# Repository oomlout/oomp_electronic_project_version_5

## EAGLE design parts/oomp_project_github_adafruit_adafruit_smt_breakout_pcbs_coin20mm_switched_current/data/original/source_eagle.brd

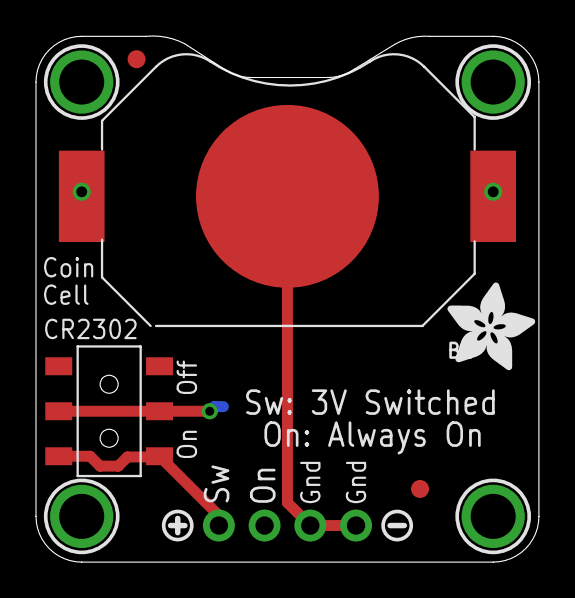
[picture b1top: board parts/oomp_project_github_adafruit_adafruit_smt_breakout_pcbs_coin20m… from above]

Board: 2 copper layers, 27.9 x 29.2 mm, 12 parts (0 on the bottom side), 3 nets.

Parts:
B1: CR2032_SMT_BAT-HLD-001
CN1: 1X4-CLEANBIG; 1X04-CLEANBIG
FID1, FID2: FIDUCIAL""; FIDUCIAL_1MM
SW1: EG1390
U$1, U$2, U$3, U$5: MOUNTINGHOLE2.5; MOUNTINGHOLE_2.5_PLATED
U$6: SYMBOL_PLUS
U$7: SYMBOL_MINUS
U$8: ADAFRUIT_5MM

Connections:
3V: B1.+$1, B1.+$2, CN1.3, SW1.P1, SW1.P2
GND: B1.-, CN1.1, CN1.2
unnamed: CN1.4, SW1.S1, SW1.S2

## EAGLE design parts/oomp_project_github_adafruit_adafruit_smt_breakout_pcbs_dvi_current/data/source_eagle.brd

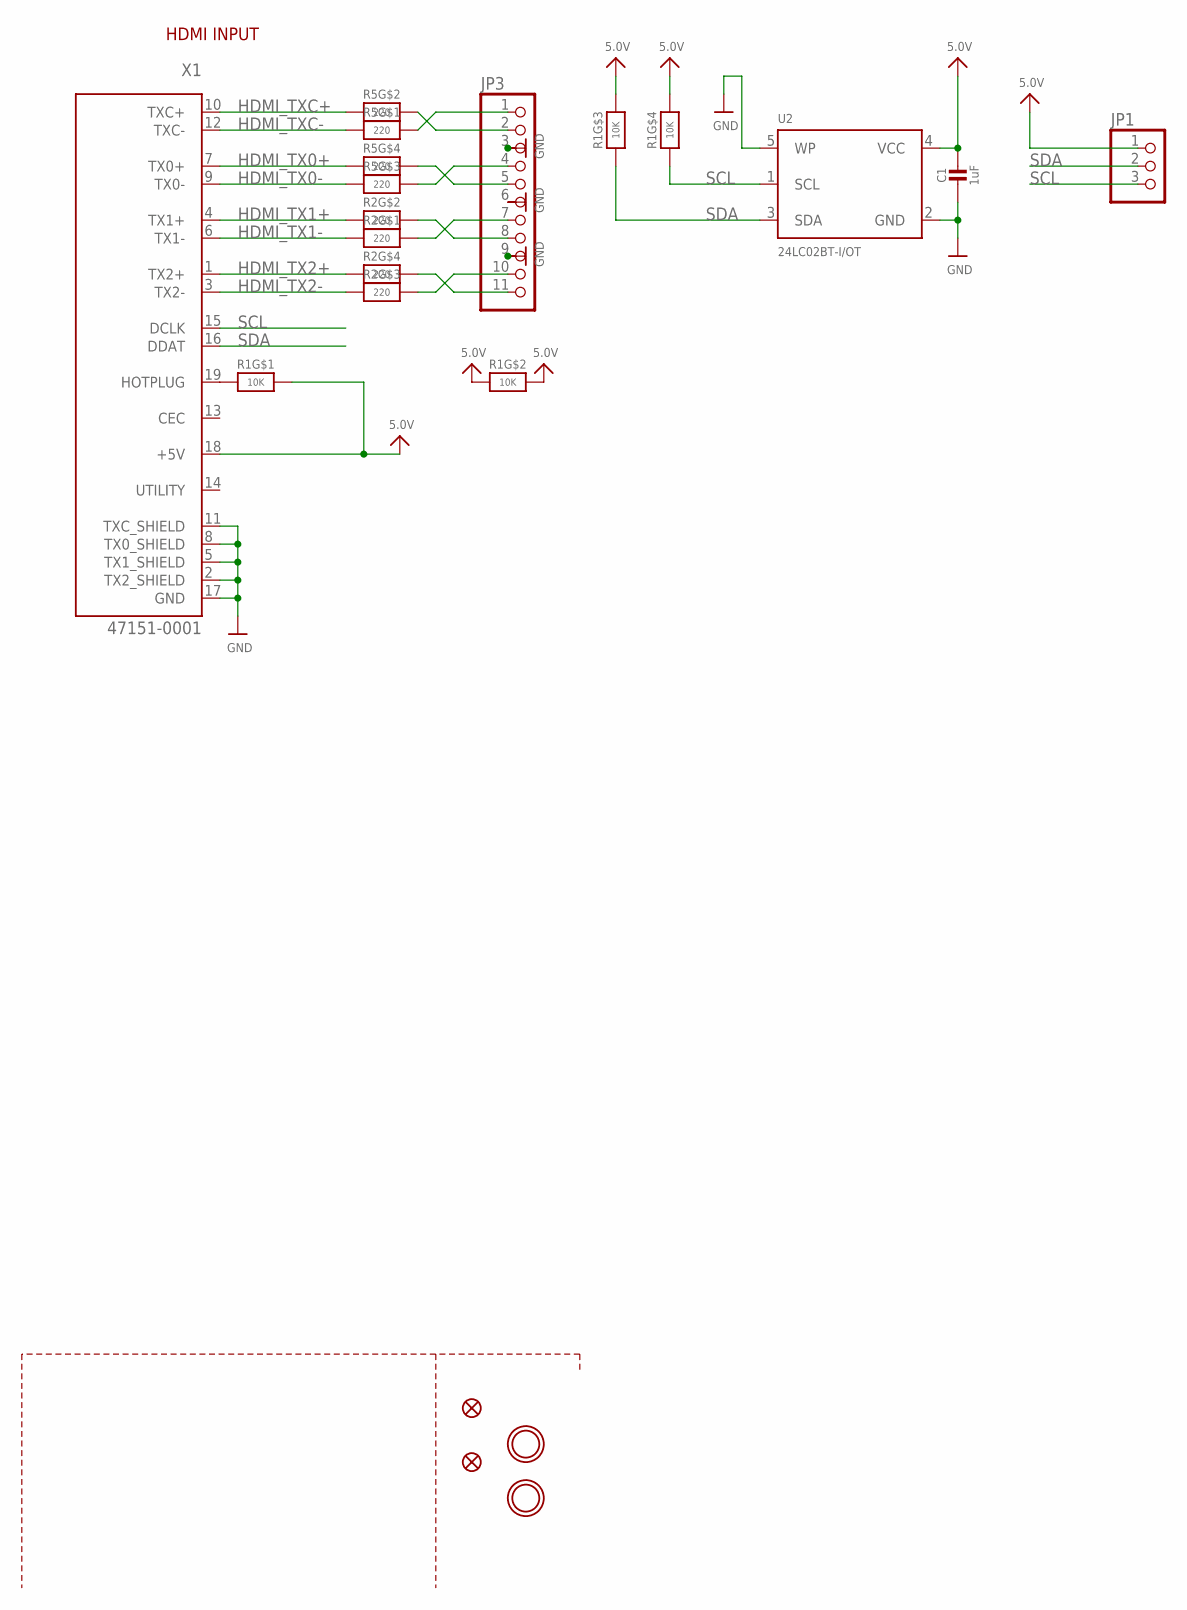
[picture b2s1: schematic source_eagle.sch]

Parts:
C1: 1uF; 0603-NO
FID1, FID2: FIDUCIAL_1MM
JP1: HEADER-1X3ROUND; 1X03_ROUND
JP3: HEADER-1X11; 1X11_ROUND
R1: 10K; RESPACK_4X0603
R2, R5: 220; RESPACK_4X0603
U2: 24LC02BT-I/OT; SOT23-5
U$32, U$33: MOUNTINGHOLE2.5; MOUNTINGHOLE_2.5_PLATED
X1: 47151-0001; HDMI_MOLEX_47151-0001

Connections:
5.0V: C1.1, JP1.1, R1.2 (1), R1.5 (2), R1.6 (2), R1.7 (2), R1.8 (2), U2.4 (VCC), X1.18 (+5V)
GND: C1.2, JP3.3, JP3.6, JP3.9, U2.2 (GND), U2.5 (WP), X1.2 (TX2_SHIELD), X1.5 (TX1_SHIELD), X1.8 (TX0_SHIELD), X1.11 (TXC_SHIELD), X1.17 (GND), X1.P$1 (GND), X1.P$2 (GND), X1.P$3 (GND), X1.P$4 (GND)
HDMI_TX0+: R5.4 (1), X1.7 (TX0+)
HDMI_TX0-: R5.3 (1), X1.9 (TX0-)
HDMI_TX1+: R2.2 (1), X1.4 (TX1+)
HDMI_TX1-: R2.1, X1.6 (TX1-)
HDMI_TX2+: R2.4 (1), X1.1 (TX2+)
HDMI_TX2-: R2.3 (1), X1.3 (TX2-)
HDMI_TXC+: R5.2 (1), X1.10 (TXC+)
HDMI_TXC-: R5.1, X1.12 (TXC-)
unnamed: R1.1, X1.19 (HOTPLUG)
SCL: JP1.3, R1.4 (1), U2.1 (SCL), X1.15 (DCLK)
SDA: JP1.2, R1.3 (1), U2.3 (SDA), X1.16 (DDAT)
TX0+: JP3.5, R5.5 (2)
TX0-: JP3.4, R5.6 (2)
TX1+: JP3.8, R2.7 (2)
TX1-: JP3.7, R2.8 (2)
TX2+: JP3.11, R2.5 (2)
TX2-: JP3.10, R2.6 (2)
TXC+: JP3.2, R5.7 (2)
TXC-: JP3.1, R5.8 (2)

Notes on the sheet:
HDMI INPUT

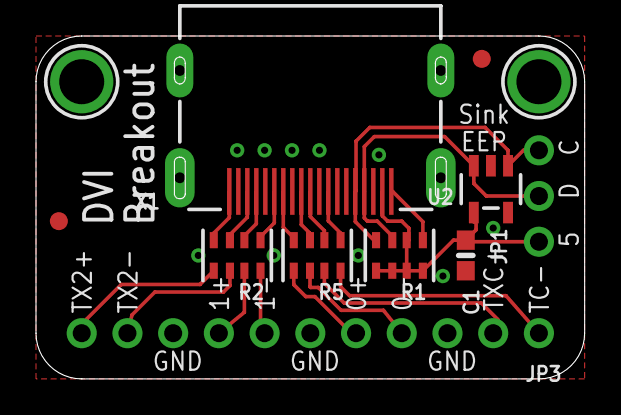
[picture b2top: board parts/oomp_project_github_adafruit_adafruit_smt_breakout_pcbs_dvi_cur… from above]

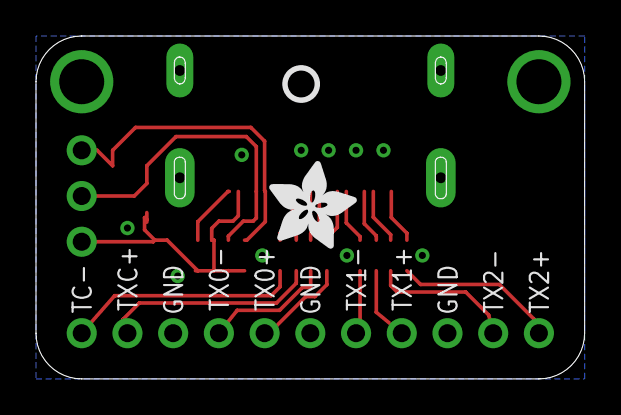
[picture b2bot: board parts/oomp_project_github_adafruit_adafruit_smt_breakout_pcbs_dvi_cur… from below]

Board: 2 copper layers, 30.5 x 19.1 mm, 14 parts (2 on the bottom side), 21 nets.

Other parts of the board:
U$6: ADAFRUIT_5MM
U$73: PCBFEAT-REV-040

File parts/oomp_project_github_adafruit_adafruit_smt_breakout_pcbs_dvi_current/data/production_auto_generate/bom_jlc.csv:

Comment,Designator,Footprint,LCSC Part #
,JP1,DVI-import-fps:1X03_ROUND,C49257
,JP3,DVI-import-fps:1X11_ROUND,C2894934
,U$6,DVI-import-fps:ADAFRUIT_5MM,
,U$73,DVI-import-fps:PCBFEAT-REV-040,
10K,R1,DVI-import-fps:RESPACK_4X0603,C98220
1uF,C1,DVI-import-fps:0603-NO,C5673
220,"R2,R5",DVI-import-fps:RESPACK_4X0603,C2907127
24LC02BT-I/OT,U2,DVI-import-fps:SOT23-5,
47151-0001,X1,DVI-import-fps:HDMI_MOLEX_47151-0001,

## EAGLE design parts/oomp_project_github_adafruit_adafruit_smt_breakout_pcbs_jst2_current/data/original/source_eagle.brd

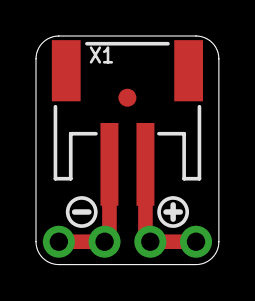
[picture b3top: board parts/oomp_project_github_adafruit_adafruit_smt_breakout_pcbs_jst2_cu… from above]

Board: 2 copper layers, 10.2 x 12.7 mm, 6 parts (1 on the bottom side), 2 nets.

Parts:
FID1: FIDUCIAL""; FIDUCIAL_1MM
JP1: PADS-4
U$1: SYMBOL_PLUS
U$2: SYMBOL_MINUS
U$4: ADAFRUIT_3.5MM
X1: JSTPH2

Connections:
unnamed: JP1.1, JP1.2, X1.1
unnamed: JP1.3, JP1.4, X1.2

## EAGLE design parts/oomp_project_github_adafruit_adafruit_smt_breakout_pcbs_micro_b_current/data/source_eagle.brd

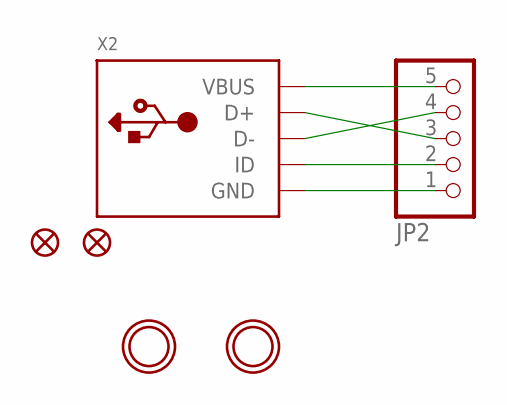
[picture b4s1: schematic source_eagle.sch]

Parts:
FID1, FID2: FIDUCIAL""; FIDUCIAL_1MM
JP2: HEADER-1X570MIL; 1X05_ROUND_70
U$1, U$2: MOUNTINGHOLE2.5; MOUNTINGHOLE_2.5_PLATED
X2: USBMICRO_20329; 4UCONN_20329

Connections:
D+: JP2.3, X2.D+
D-: JP2.4, X2.D-
GND: JP2.1, X2.BASE@1 (GND), X2.BASE@2 (GND), X2.GND, X2.SPRT@1 (GND), X2.SPRT@2 (GND), X2.SPRT@3 (GND), X2.SPRT@4 (GND)
ID: JP2.2, X2.ID
VBUS: JP2.5, X2.VBUS

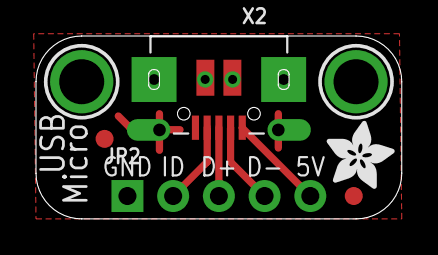
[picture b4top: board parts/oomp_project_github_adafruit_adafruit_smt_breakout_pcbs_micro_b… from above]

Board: 2 copper layers, 20.3 x 10.2 mm, 7 parts (0 on the bottom side), 5 nets.

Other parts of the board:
U$4: ADAFRUIT_3.5MM

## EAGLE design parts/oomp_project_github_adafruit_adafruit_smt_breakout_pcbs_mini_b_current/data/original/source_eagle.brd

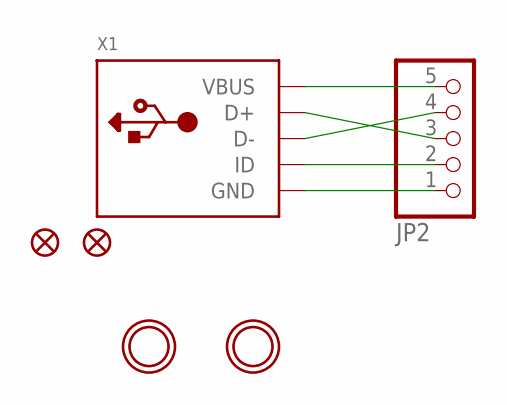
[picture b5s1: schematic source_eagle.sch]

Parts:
FID1, FID2: FIDUCIAL""; FIDUCIAL_1MM
JP2: HEADER-1X570MIL; 1X05_ROUND_70
U$1, U$2: MOUNTINGHOLE2.5; MOUNTINGHOLE_2.5_PLATED
X1: USBMINIBLARGE; USB-MINIB_LARGER

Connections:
D+: JP2.3, X1.D+
D-: JP2.4, X1.D-
GND: JP2.1, X1.GND, X1.GND1 (GND), X1.GND2 (GND), X1.GND3 (GND), X1.GND4 (GND)
ID: JP2.2, X1.ID
VBUS: JP2.5, X1.VBUS

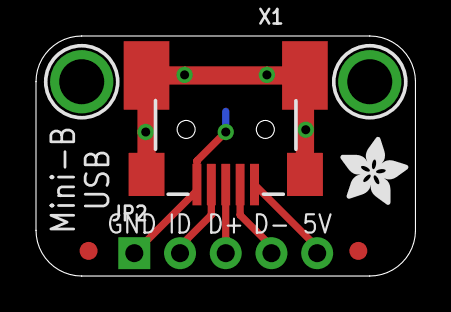
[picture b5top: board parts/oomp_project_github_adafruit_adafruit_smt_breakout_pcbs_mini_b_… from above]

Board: 2 copper layers, 21.1 x 13.3 mm, 7 parts (0 on the bottom side), 5 nets.

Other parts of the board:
U$4: ADAFRUIT_3.5MM

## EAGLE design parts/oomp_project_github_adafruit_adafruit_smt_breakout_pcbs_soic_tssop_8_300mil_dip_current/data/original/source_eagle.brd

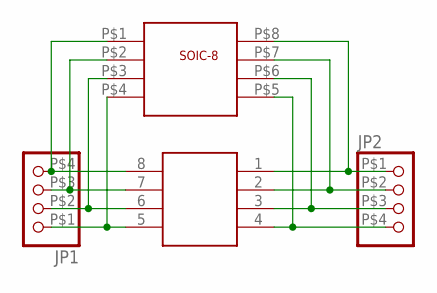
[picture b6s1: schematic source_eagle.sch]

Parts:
JP1, JP2: PINHD-1X4THIN; HEADER1X4
U$1: SO-8; SO-08NMW
U$2: TSSOP-8; TSSOP-8NM

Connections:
unnamed: JP1.P$4 (4), U$1.P$1, U$2.8
unnamed: JP1.P$3 (3), U$1.P$2, U$2.7
unnamed: JP1.P$2 (2), U$1.P$3, U$2.6
unnamed: JP1.P$1 (1), U$1.P$4, U$2.5
unnamed: JP2.P$4 (4), U$1.P$5, U$2.4
unnamed: JP2.P$3 (3), U$1.P$6, U$2.3
unnamed: JP2.P$2 (2), U$1.P$7, U$2.2
unnamed: JP2.P$1 (1), U$1.P$8, U$2.1

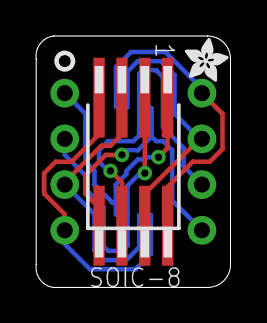
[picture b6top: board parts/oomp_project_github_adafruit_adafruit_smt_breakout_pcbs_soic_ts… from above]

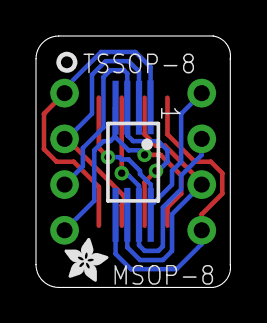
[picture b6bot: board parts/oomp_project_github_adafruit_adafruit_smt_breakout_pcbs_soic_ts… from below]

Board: 2 copper layers, 10.8 x 14.0 mm, 6 parts (2 on the bottom side), 8 nets.

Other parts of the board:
U$3, U$4: ADAFRUIT_2.5MM

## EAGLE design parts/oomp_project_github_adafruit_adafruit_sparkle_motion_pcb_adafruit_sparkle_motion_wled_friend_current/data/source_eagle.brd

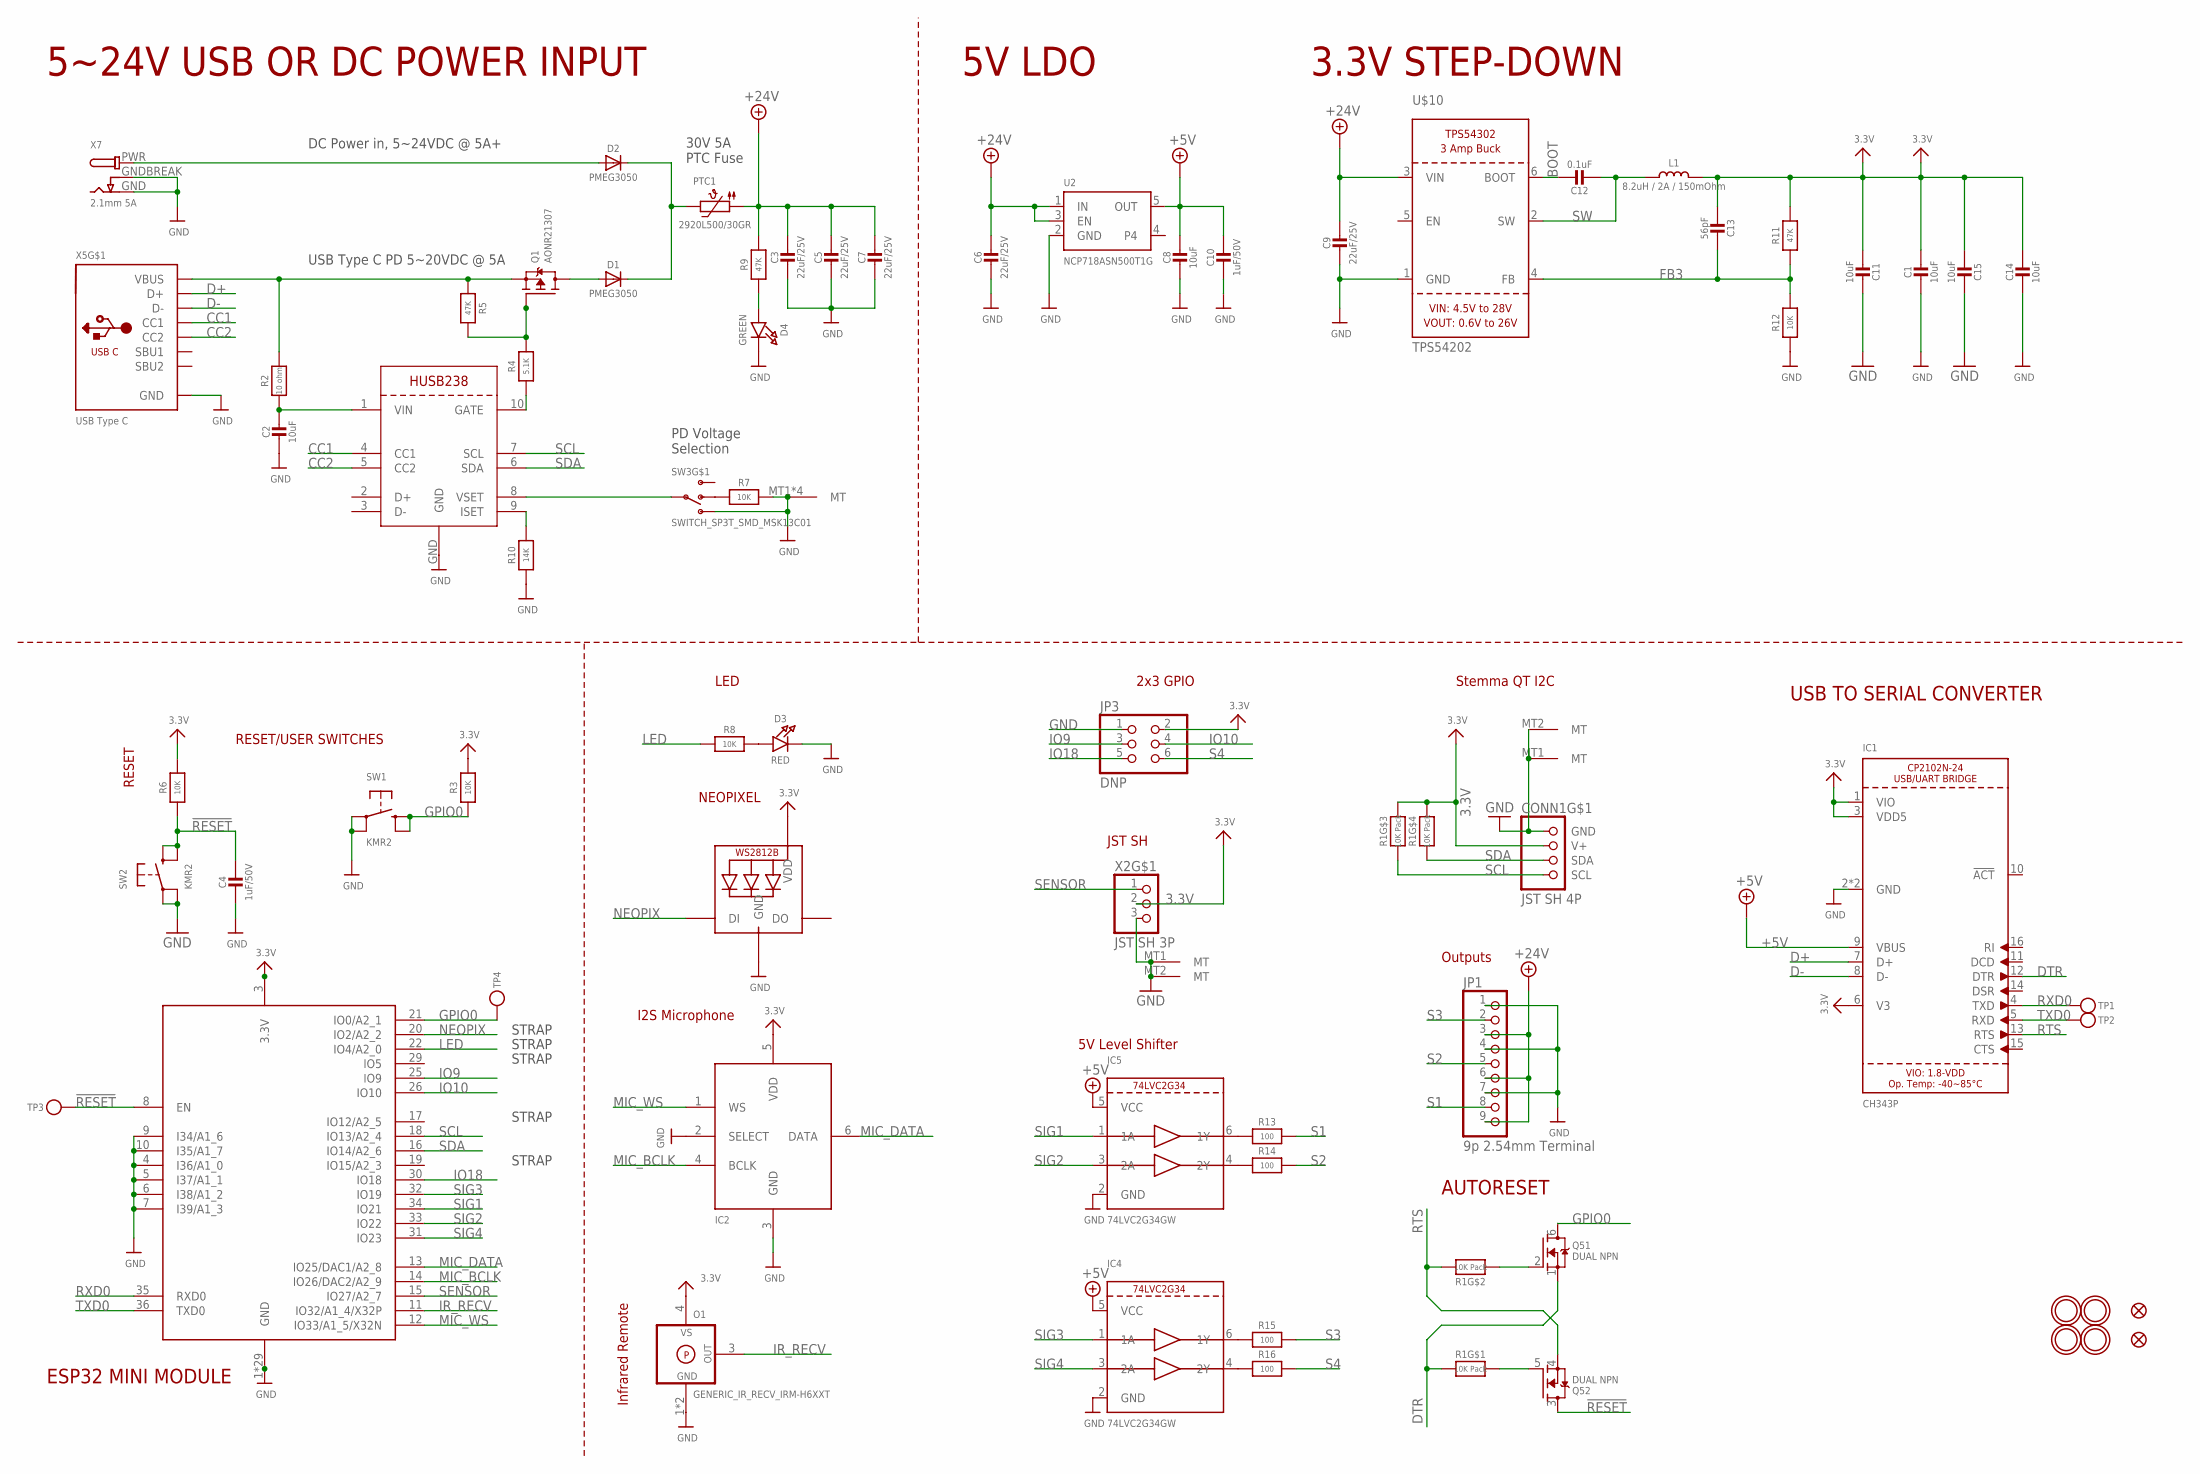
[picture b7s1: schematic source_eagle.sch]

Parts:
C1, C2, C8, C11, C14, C15: 10uF; 0805-NO
C3, C5, C6, C7, C9: 22uF/25V; 0805-NO
C4, C10: 1uF/50V; 0603-NO
C12: 0.1uF; 0603-NO
C13: 56pF; 0603-NO
CONN1: JST SH 4P; JST_SH4
D1, D2: PMEG3050; SOD-128
D3: RED; CHIPLED_0603_NOOUTLINE
D4: GREEN; CHIPLED_0603_NOOUTLINE
IC1: CH343P; QFN16_3MM
IC2: ICS-43434; SPH0645LM4H
IC4, IC5: 74LVC2G34GW; SC70-6L
JP1: 9p 2.54mm Terminal; 1X09_2.54MMTERMINAL
JP3: DNP; 2X03_ROUND_70MIL
L1: 8.2uH / 2A / 150mOhm; INDUCTOR_5X5MM_NR5040_NOTHERMALS
LED1: WS2812B_SK6805_1515; SK6805_1515
O1: GENERIC_IR_RECV_IRM-H6XXT; IRM-H6XXT
PTC1: 2920L500/30GR; PTC2920
Q1: AONR21307; POWERDI3333
Q5: DUAL NPN; SOT363; JLC_ROTATION 0
R1: 10K Pack; RESPACK_4X0603
R2: 10 ohm; 0603-NO
R3, R6, R7, R8, R12: 10K; 0603-NO
R4: 5.1K; 0603-NO
R5, R9, R11: 47K; 0603-NO
R10: 14K; 0603-NO
R13, R14, R15, R16: 100; 0603-NO
SW1, SW2: KMR2; BTN_RKB2_4.6X2.8
SW3: SWITCH_SP3T_SMD_MSK13C01; MSK-13C01
TP1, TP2, TP3, TP4: TESTPOINTROUND1.5MM; TESTPOINT_ROUND_1.5MM
U2: NCP718ASN500T1G; SOT23-5; JLC_ROTATION 0
U$10: TPS54202; SOT23-6
U$14, U$20, U$28, U$31: MOUNTINGHOLE2.5; MOUNTINGHOLE_2.5_PLATED
U$34, U$35: FIDUCIAL_1MM
X2: JST SH 3P; JST_SH3
X3: HUSB238; DFN10_3X3MM
X4: ESP32-MINI-1
X5: USB Type C; USB_C_CUSB31-CFM2AX-01-X
X7: 2.1mm 5A; DCJACK_2MM_PTH

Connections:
3.3V: C1.1, C11.1, C13.2, C14.1, C15.1, CONN1.2 (V+), IC1.1 (VIO), IC1.3 (VDD5), IC1.6 (V3), IC2.5 (VDD), JP3.2, L1.P$2 (2), LED1.2 (VDD), O1.4 (VS), R1.5 (2), R1.6 (2), R3.2, R6.2, R11.2, X2.2, X4.3 (3.3V)
!RESET: C4.1, Q5.3 (D), R6.1, SW2.B (S), SW2.B' (S1), TP3.P$1, X4.8 (EN)
+5V: C8.1, C10.1, IC1.9 (VBUS), IC4.5 (VCC), IC5.5 (VCC), U2.5 (OUT)
+24V: C3.1, C5.1, C6.1, C7.1, C9.1, JP1.3, JP1.6, JP1.9, PTC1.P$1 (1), R9.2, U2.1 (IN), U2.3 (EN), U$10.3 (VIN)
BOOT: C12.1, U$10.6 (BOOT)
CC1: X3.4 (CC1), X5.A5 (CC1)
CC2: X3.5 (CC2), X5.B5 (CC2)
D+: IC1.7 (D+), X5.A6 (D+), X5.B6 (D+)
D-: IC1.8 (D-), X5.A7 (D-), X5.B7 (D-)
DTR: IC1.12 (DTR), Q5.1 (S), R1.1
FB3: C13.1, R11.1, R12.2, U$10.4 (FB)
GND: C1.2, C2.2, C3.2, C4.2, C5.2, C6.2, C7.2, C8.2, C9.2, C10.2, C11.2, C14.2, C15.2, CONN1.1 (GND), CONN1.MT1 (MT), CONN1.MT2 (MT), D3.C, D4.C, IC1.2 (GND), IC1.THERMAL (GND), IC2.2 (SELECT), IC2.3 (GND), IC4.2 (GND), IC5.2 (GND), JP1.1, JP1.4, JP1.7, JP3.1, LED1.4 (GND), O1.1 (GND), O1.2 (GND), R7.1, R10.1, R12.1, SW1.A, SW1.A' (P1), SW2.A, SW2.A' (P1), SW3.4 (3), SW3.MT1 (MT), SW3.MT2 (MT), SW3.MT3 (MT), SW3.MT4 (MT), U2.2 (GND), U$10.1 (GND), X2.3, X2.MT1 (MT), X2.MT2 (MT), X3.GND, X4.1 (GND), X4.2 (GND), X4.4 (I36/A1_0), X4.5 (I37/A1_1), X4.6 (I38/A1_2), X4.7 (I39/A1_3), X4.9 (I34/A1_6), X4.10 (I35/A1_7), X4.27 (GND), X4.38 (GND), X4.39 (GND), X4.40 (GND), X4.41 (GND), X4.42 (GND), X4.43 (GND), X4.44 (GND), X4.45 (GND), X4.46 (GND), X4.47 (GND), X4.48 (GND), X4.49 (GND), X4.50 (GND), X4.51 (GND), X4.52 (GND), X4.53 (GND), X4.54 (GND), X4.55 (GND), X4.56 (GND), X4.57 (GND), X4.58 (GND), X4.59 (GND), X4.60 (GND), X4.61 (GND), X4.62 (GND), X4.63 (GND), X5.A1B12 (GND), X5.B1A12 (GND), X7.GND, X7.GNDBREAK
GPIO0: Q5.6 (D), R3.1, SW1.B (S), SW1.B' (S1), TP4.P$1, X4.21 (IO0/A2_1)
IO9: JP3.3, X4.25 (IO9)
IO10: JP3.4, X4.26 (IO10)
IO18: JP3.5, X4.30 (IO18)
IR_RECV: O1.3 (OUT), X4.11 (IO32/A1_4/X32P)
LED: R8.1, X4.22 (IO4/A2_0)
MIC_BCLK: IC2.4 (BCLK), X4.14 (IO26/DAC2/A2_9)
MIC_DATA: IC2.6 (DATA), X4.13 (IO25/DAC1/A2_8)
MIC_WS: IC2.1 (WS), X4.12 (IO33/A1_5/X32N)
unnamed: D3.A, R8.2
unnamed: C2.1, R2.1, X3.1 (VIN)
unnamed: Q1.4 (G), R4.2, R5.2
unnamed: R4.1, X3.10 (GATE)
unnamed: SW3.3, X3.8 (VSET)
unnamed: R7.2, SW3.2
unnamed: Q5.5 (G), R1.8 (2)
unnamed: Q5.2 (G), R1.2 (1)
unnamed: D2.A, X7.PWR
unnamed: IC5.6 (1Y), R13.1
unnamed: IC5.4 (2Y), R14.1
unnamed: R10.2, X3.9 (ISET)
unnamed: D1.C, D2.C, PTC1.P$2 (2)
unnamed: D1.A, Q1.5678 (D)
unnamed: D4.A, R9.1
unnamed: IC4.6 (1Y), R15.1
unnamed: IC4.4 (2Y), R16.1
NEOPIX: LED1.1 (DI), X4.20 (IO2/A2_2)
RTS: IC1.13 (RTS), Q5.4 (S), R1.7 (2)
RXD0: IC1.4 (TXD), TP1.P$1, X4.35 (RXD0)
S1: JP1.8, R13.2
S2: JP1.5, R14.2
S3: JP1.2, R15.2
S4: JP3.6, R16.2
SCL: CONN1.4 (SCL), R1.3 (1), X3.7 (SCL), X4.18 (IO13/A2_4)
SDA: CONN1.3 (SDA), R1.4 (1), X3.6 (SDA), X4.16 (IO14/A2_6)
SENSOR: X2.1, X4.15 (IO27/A2_7)
SIG1: IC5.1 (1A), X4.34 (IO21)
SIG2: IC5.3 (2A), X4.33 (IO22)
SIG3: IC4.1 (1A), X4.32 (IO19)
SIG4: IC4.3 (2A), X4.31 (IO23)
SW: C12.2, L1.P$1 (1), U$10.2 (SW)
TXD0: IC1.5 (RXD), TP2.P$1, X4.36 (TXD0)
VBUS1: Q1.1 (S), Q1.2 (S), Q1.3 (S), R2.2, R5.1, X5.A4B9 (VBUS), X5.B4A9 (VBUS)

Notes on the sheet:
5~24V USB OR DC POWER INPUT
RESET
LED
NEOPIXEL
ESP32 MINI MODULE
RESET/USER SWITCHES
AUTORESET
USB TO SERIAL CONVERTER
DC Power in, 5~24VDC @ 5A+
USB Type C PD 5~20VDC @ 5A
30V 5A PTC Fuse
PD Voltage Selection
5V LDO
3.3V STEP-DOWN
STRAP
I2S Microphone
Infrared Remote
2x3 GPIO
JST SH
5V Level Shifter
Stemma QT I2C
Outputs

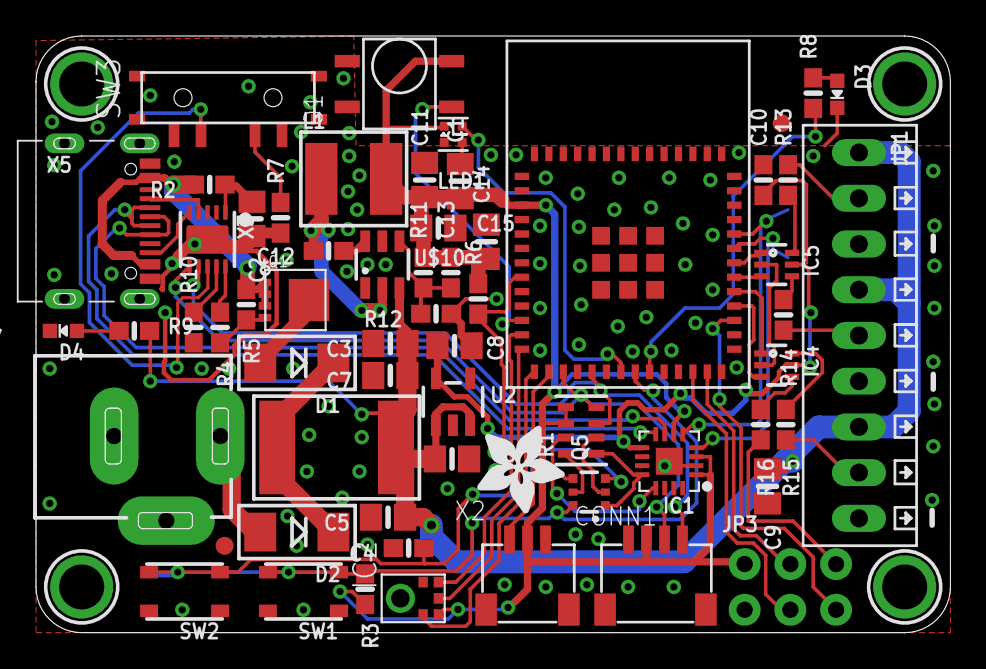
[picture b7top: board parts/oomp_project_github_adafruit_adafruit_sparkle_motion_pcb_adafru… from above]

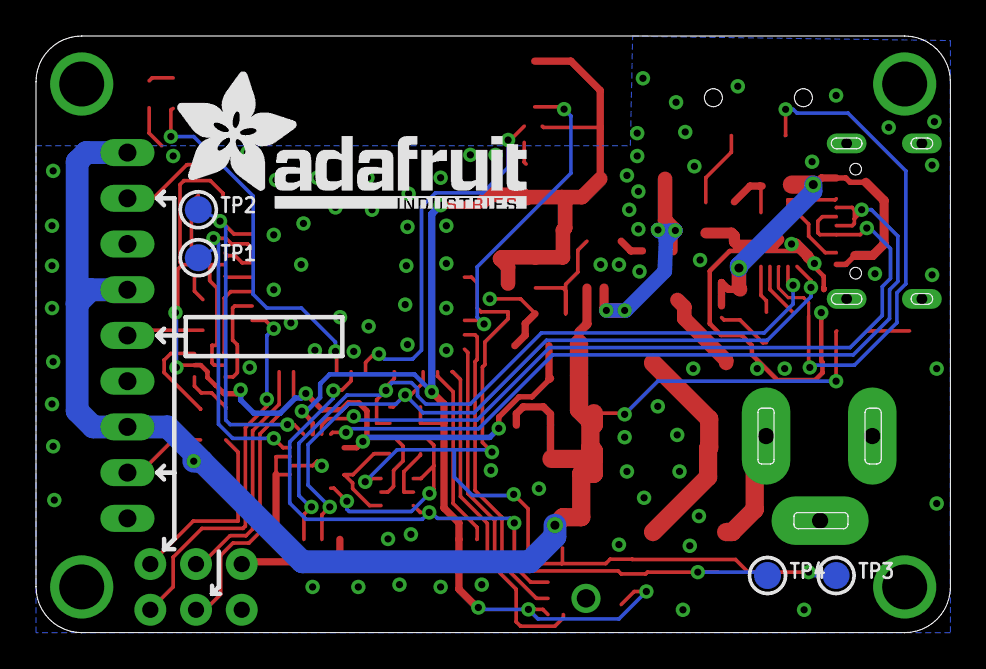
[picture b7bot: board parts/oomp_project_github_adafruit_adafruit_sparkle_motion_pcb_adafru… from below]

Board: 2 copper layers, 50.8 x 33.1 mm, 123 parts (36 on the bottom side), 55 nets.

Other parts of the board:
PLABEL0: PLABEL0
PLABEL1: PLABEL1
PLABEL2: PLABEL2
PLABEL3: PLABEL3
PLABEL4: PLABEL4
PLABEL6: PLABEL6
PLABEL7: PLABEL7
PLABEL8: PLABEL8
PLABEL9: PLABEL9
PLABEL10: PLABEL10
PLABEL11: PLABEL11
PLABEL13: PLABEL13
PLABEL14: PLABEL14
PLABEL16: PLABEL16
PLABEL17: PLABEL17
PLABEL19: PLABEL19
PLABEL20: PLABEL20
PLABEL21: PLABEL21
PLABEL22: PLABEL22
PLABEL23: PLABEL23
PLABEL24: PLABEL24
PLABEL25: PLABEL25
PLABEL26: PLABEL26
PLABEL27: PLABEL27
PLABEL28: PLABEL28
PLABEL29: PLABEL29
PLABEL30: PLABEL30
PLABEL31: PLABEL31
PLABEL32: PLABEL32
PLABEL33: PLABEL33
PLABEL34: PLABEL34
PLABEL35: PLABEL35
PLABEL36: PLABEL36
PLABEL37: PLABEL37
PLABEL38: PLABEL38
PLABEL39: PLABEL39
PLABEL40: PLABEL40
PLABEL41: PLABEL41
PLABEL42: PLABEL42
PLABEL43: PLABEL43
PLABEL44: PLABEL44
PLABEL45: PLABEL45
PLABEL46: PLABEL46
PLABEL47: PLABEL47
PLABEL48: PLABEL48
PLABEL49: PLABEL49
PLABEL50: PLABEL50
PLABEL51: PLABEL51
PLABEL52: PLABEL52
PLABEL53: PLABEL53
PLABEL54: PLABEL54
PLABEL55: PLABEL55
PLABEL56: PLABEL56
U$46: ADAFRUIT_5MM
U$50: ADAFRUIT_TEXT_20MM

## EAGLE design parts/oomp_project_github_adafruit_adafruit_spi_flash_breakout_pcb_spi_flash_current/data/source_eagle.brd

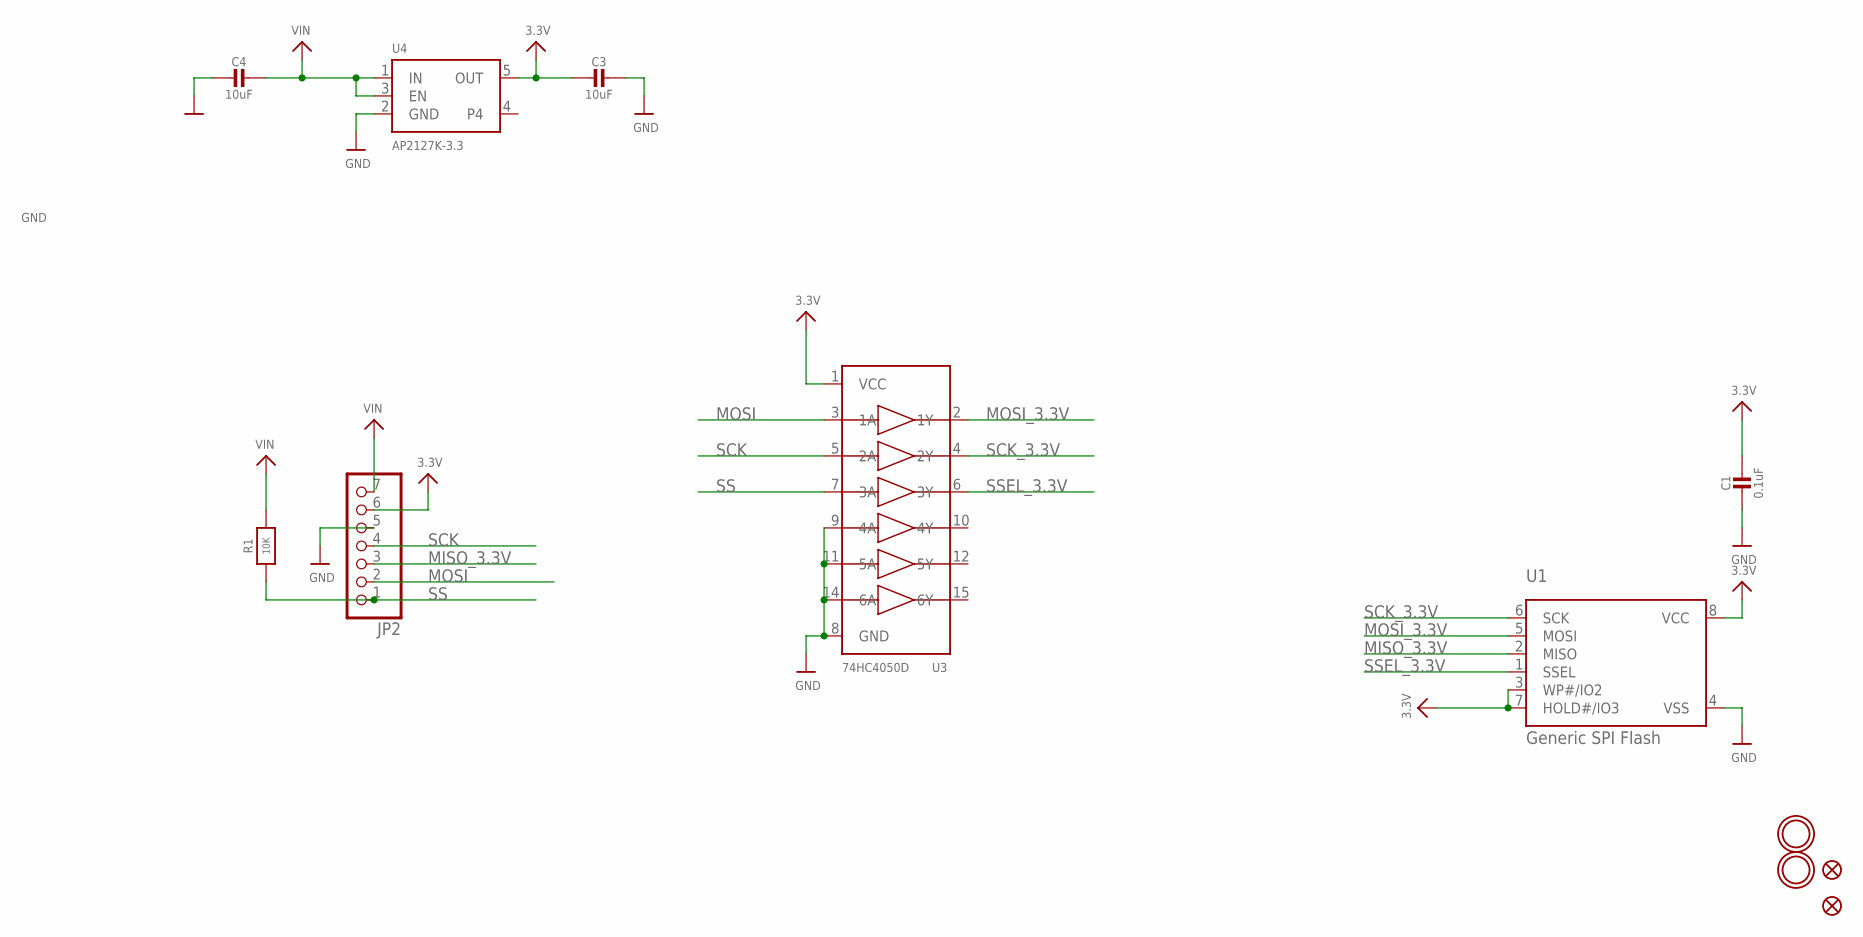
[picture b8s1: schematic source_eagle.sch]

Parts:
C1: 0.1uF; 0603-NO
C3, C4: 10uF; 0805-NO
FID2, FID3: FIDUCIAL_1MM
JP2: HEADER-1X770MIL; 1X07_ROUND_70
R1: 10K; 0603-NO
U1: Generic SPI Flash; SOIC8_208MIL
U3: 74HC4050D; TSSOP16
U4: AP2127K-3.3; SOT23-5
U$16, U$17: MOUNTINGHOLE2.5; MOUNTINGHOLE_2.5_PLATED

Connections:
3.3V: C1.1, C3.2, JP2.6, U1.3 (WP#/IO2), U1.7 (HOLD#/IO3), U1.8 (VCC), U3.1 (VCC), U4.5 (OUT)
GND: C1.2, C3.1, C4.2, JP2.5, U1.4 (VSS), U3.8 (GND), U3.9 (4A), U3.11 (5A), U3.14 (6A), U4.2 (GND)
MISO_3.3V: JP2.3, U1.2 (MISO)
MOSI: JP2.2, U3.3 (1A)
MOSI_3.3V: U1.5 (MOSI), U3.2 (1Y)
SCK: JP2.4, U3.5 (2A)
SCK_3.3V: U1.6 (SCK), U3.4 (2Y)
SS: JP2.1, R1.1, U3.7 (3A)
SSEL_3.3V: U1.1 (SSEL), U3.6 (3Y)
VIN: C4.1, JP2.7, R1.2, U4.1 (IN), U4.3 (EN)

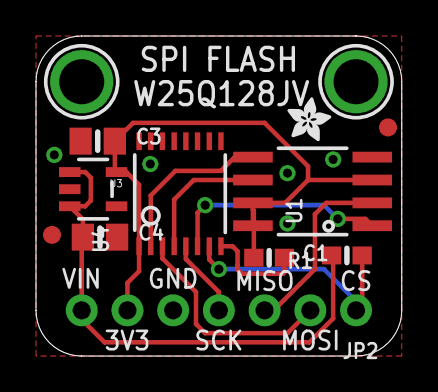
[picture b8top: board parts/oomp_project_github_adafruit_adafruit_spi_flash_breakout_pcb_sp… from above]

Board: 2 copper layers, 20.3 x 17.8 mm, 14 parts (1 on the bottom side), 10 nets.

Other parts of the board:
U$13: ADAFRUIT_2.5MM
U$21: PCBFEAT-REV-040

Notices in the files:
parts and their libraries:
microbuilder: This work is placed in the public domain, and may be freely used for commercial and non-commercial work with the following conditions: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
